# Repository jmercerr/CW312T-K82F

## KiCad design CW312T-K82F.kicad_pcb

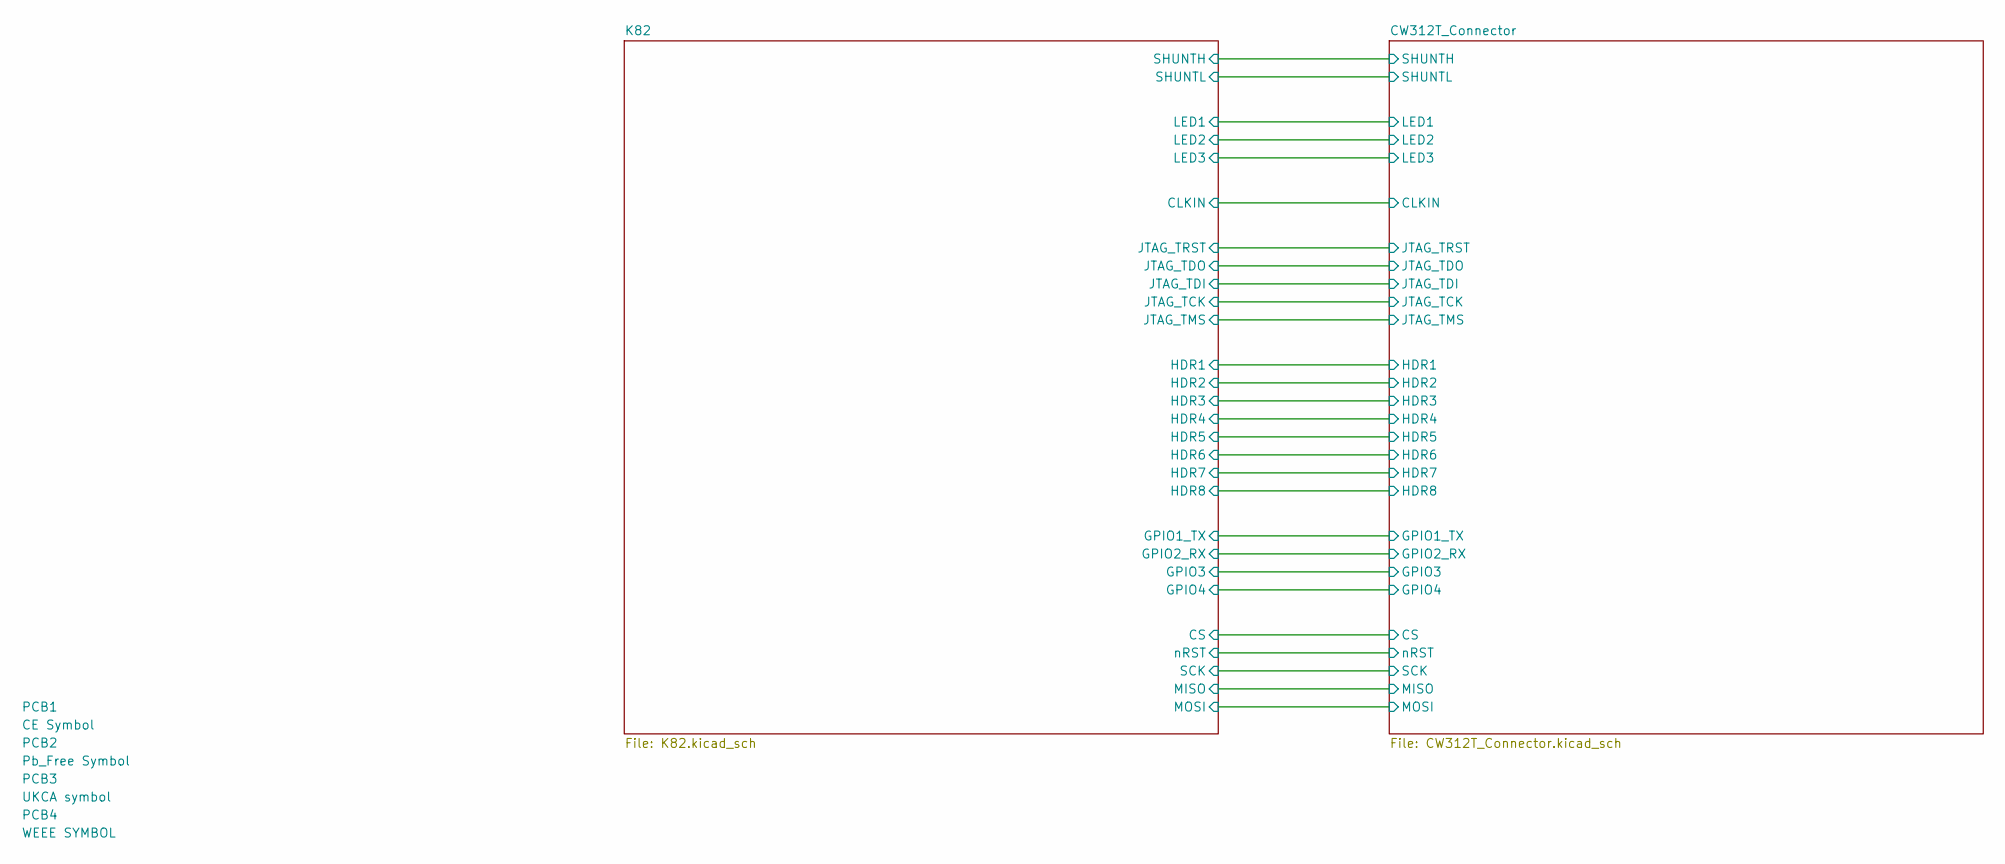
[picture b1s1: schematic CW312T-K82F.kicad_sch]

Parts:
PCB1: CE Symbol; CE-Logo_8.5x6mm_SilkScreen
PCB2: Pb_Free Symbol; Pb_Free_8.0x8.0mm_SilkScreen
PCB3: UKCA symbol; UKCA-Logo_8x8mm_SilkScreen
PCB4: WEEE SYMBOL; WEEE-Logo_5.6x8mm_SilkScreen

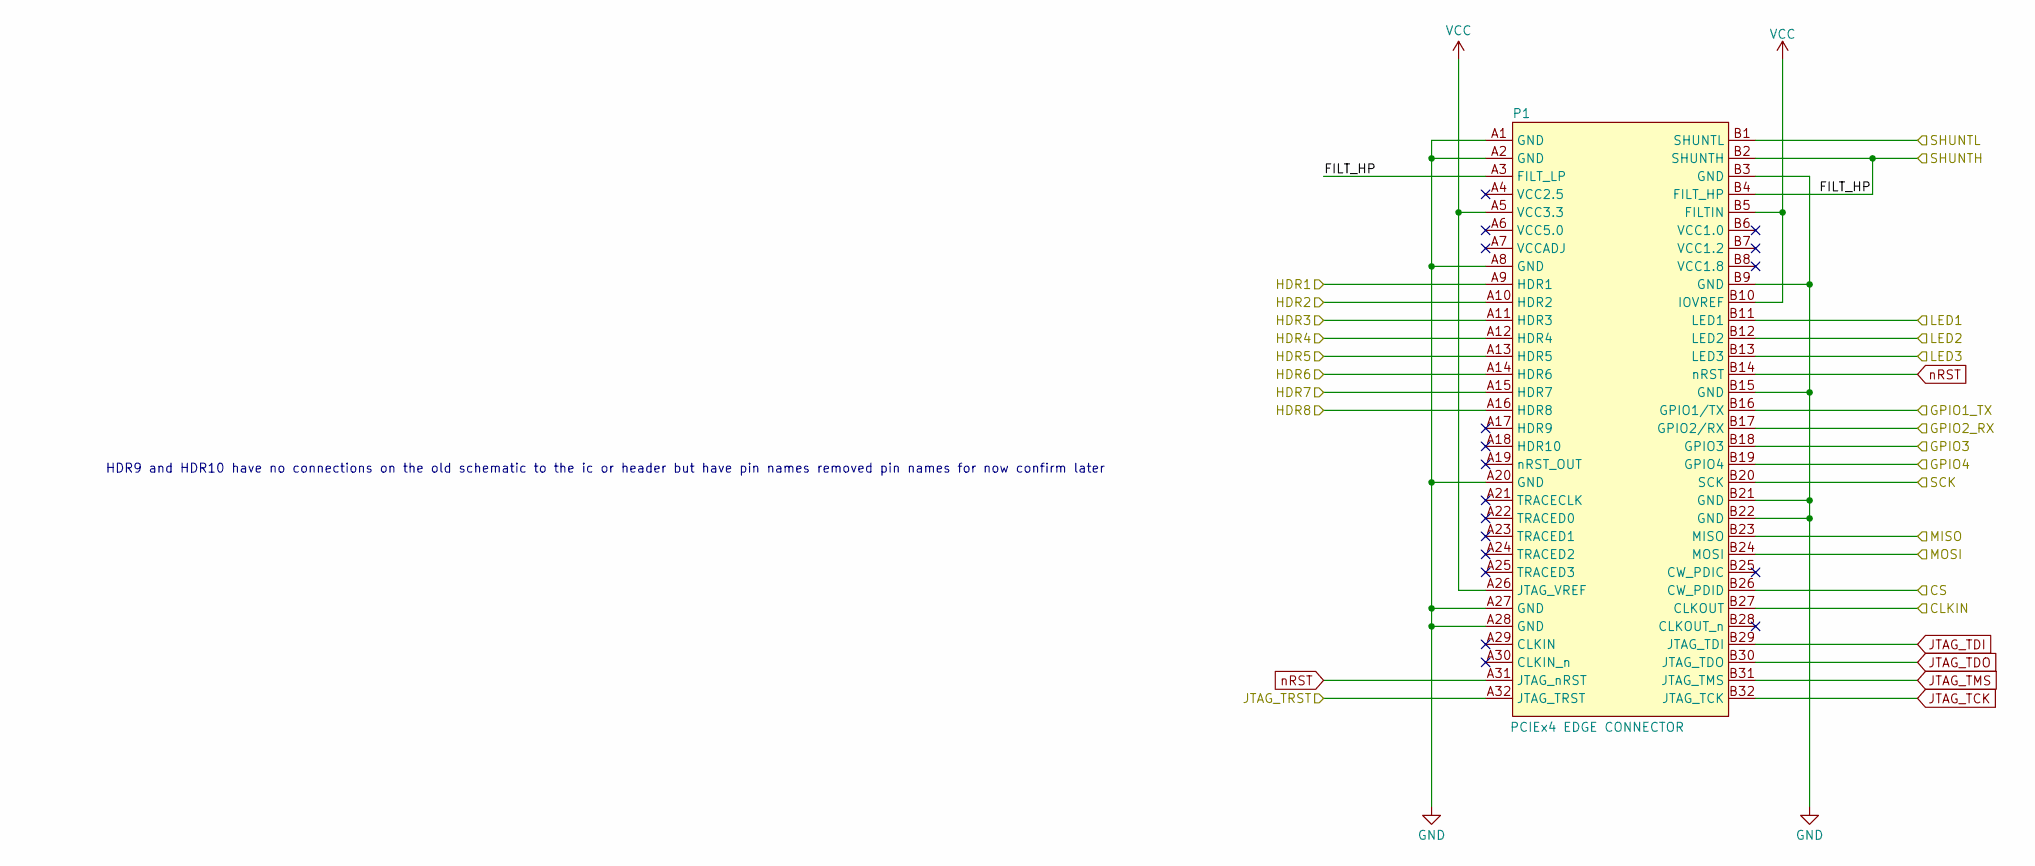
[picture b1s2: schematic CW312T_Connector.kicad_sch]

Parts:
P1: PCIEx4 EDGE CONNECTOR; CW312_Template

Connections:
/CW312T_Connector/CLKIN: P1.B27 (CLKOUT); also elsewhere on the board
/CW312T_Connector/CS: P1.B26 (CW_PDID); also elsewhere on the board
/CW312T_Connector/FILT_HP: P1.A3 (FILT_LP), P1.B2 (SHUNTH), P1.B4 (FILT_HP); also elsewhere on the board
/CW312T_Connector/GPIO1_TX: P1.B16 (GPIO1/TX); also elsewhere on the board
/CW312T_Connector/GPIO2_RX: P1.B17 (GPIO2/RX); also elsewhere on the board
/CW312T_Connector/GPIO3: P1.B18 (GPIO3); also elsewhere on the board
/CW312T_Connector/GPIO4: P1.B19 (GPIO4); also elsewhere on the board
/CW312T_Connector/HDR1: P1.A9 (HDR1); also elsewhere on the board
/CW312T_Connector/HDR2: P1.A10 (HDR2); also elsewhere on the board
/CW312T_Connector/HDR3: P1.A11 (HDR3); also elsewhere on the board
/CW312T_Connector/HDR4: P1.A12 (HDR4); also elsewhere on the board
/CW312T_Connector/HDR5: P1.A13 (HDR5); also elsewhere on the board
/CW312T_Connector/HDR6: P1.A14 (HDR6); also elsewhere on the board
/CW312T_Connector/HDR7: P1.A15 (HDR7); also elsewhere on the board
/CW312T_Connector/HDR8: P1.A16 (HDR8); also elsewhere on the board
/CW312T_Connector/JTAG_TRST: P1.A32 (JTAG_TRST); also elsewhere on the board
/CW312T_Connector/LED1: P1.B11 (LED1); also elsewhere on the board
/CW312T_Connector/LED2: P1.B12 (LED2); also elsewhere on the board
/CW312T_Connector/LED3: P1.B13 (LED3); also elsewhere on the board
/CW312T_Connector/MISO: P1.B23 (MISO); also elsewhere on the board
/CW312T_Connector/MOSI: P1.B24 (MOSI); also elsewhere on the board
/CW312T_Connector/SCK: P1.B20 (SCK); also elsewhere on the board
/CW312T_Connector/SHUNTL: P1.B1 (SHUNTL); also elsewhere on the board
GND: P1.A1 (GND), P1.A2 (GND), P1.A8 (GND), P1.A20 (GND), P1.A27 (GND), P1.A28 (GND), P1.B3 (GND), P1.B9 (GND), P1.B15 (GND), P1.B21 (GND), P1.B22 (GND); also elsewhere on the board
JTAG_TCK: P1.B32 (JTAG_TCK); also elsewhere on the board
JTAG_TDI: P1.B29 (JTAG_TDI); also elsewhere on the board
JTAG_TDO: P1.B30 (JTAG_TDO); also elsewhere on the board
JTAG_TMS: P1.B31 (JTAG_TMS); also elsewhere on the board
VCC: P1.A5 (VCC3.3), P1.A26 (JTAG_VREF), P1.B5 (FILTIN), P1.B10 (IOVREF); also elsewhere on the board
nRST: P1.A31 (JTAG_nRST), P1.B14 (nRST); also elsewhere on the board

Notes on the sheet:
HDR9 and HDR10 have no connections on the old schematic to the ic or header but have pin names removed pin names for now confirm later

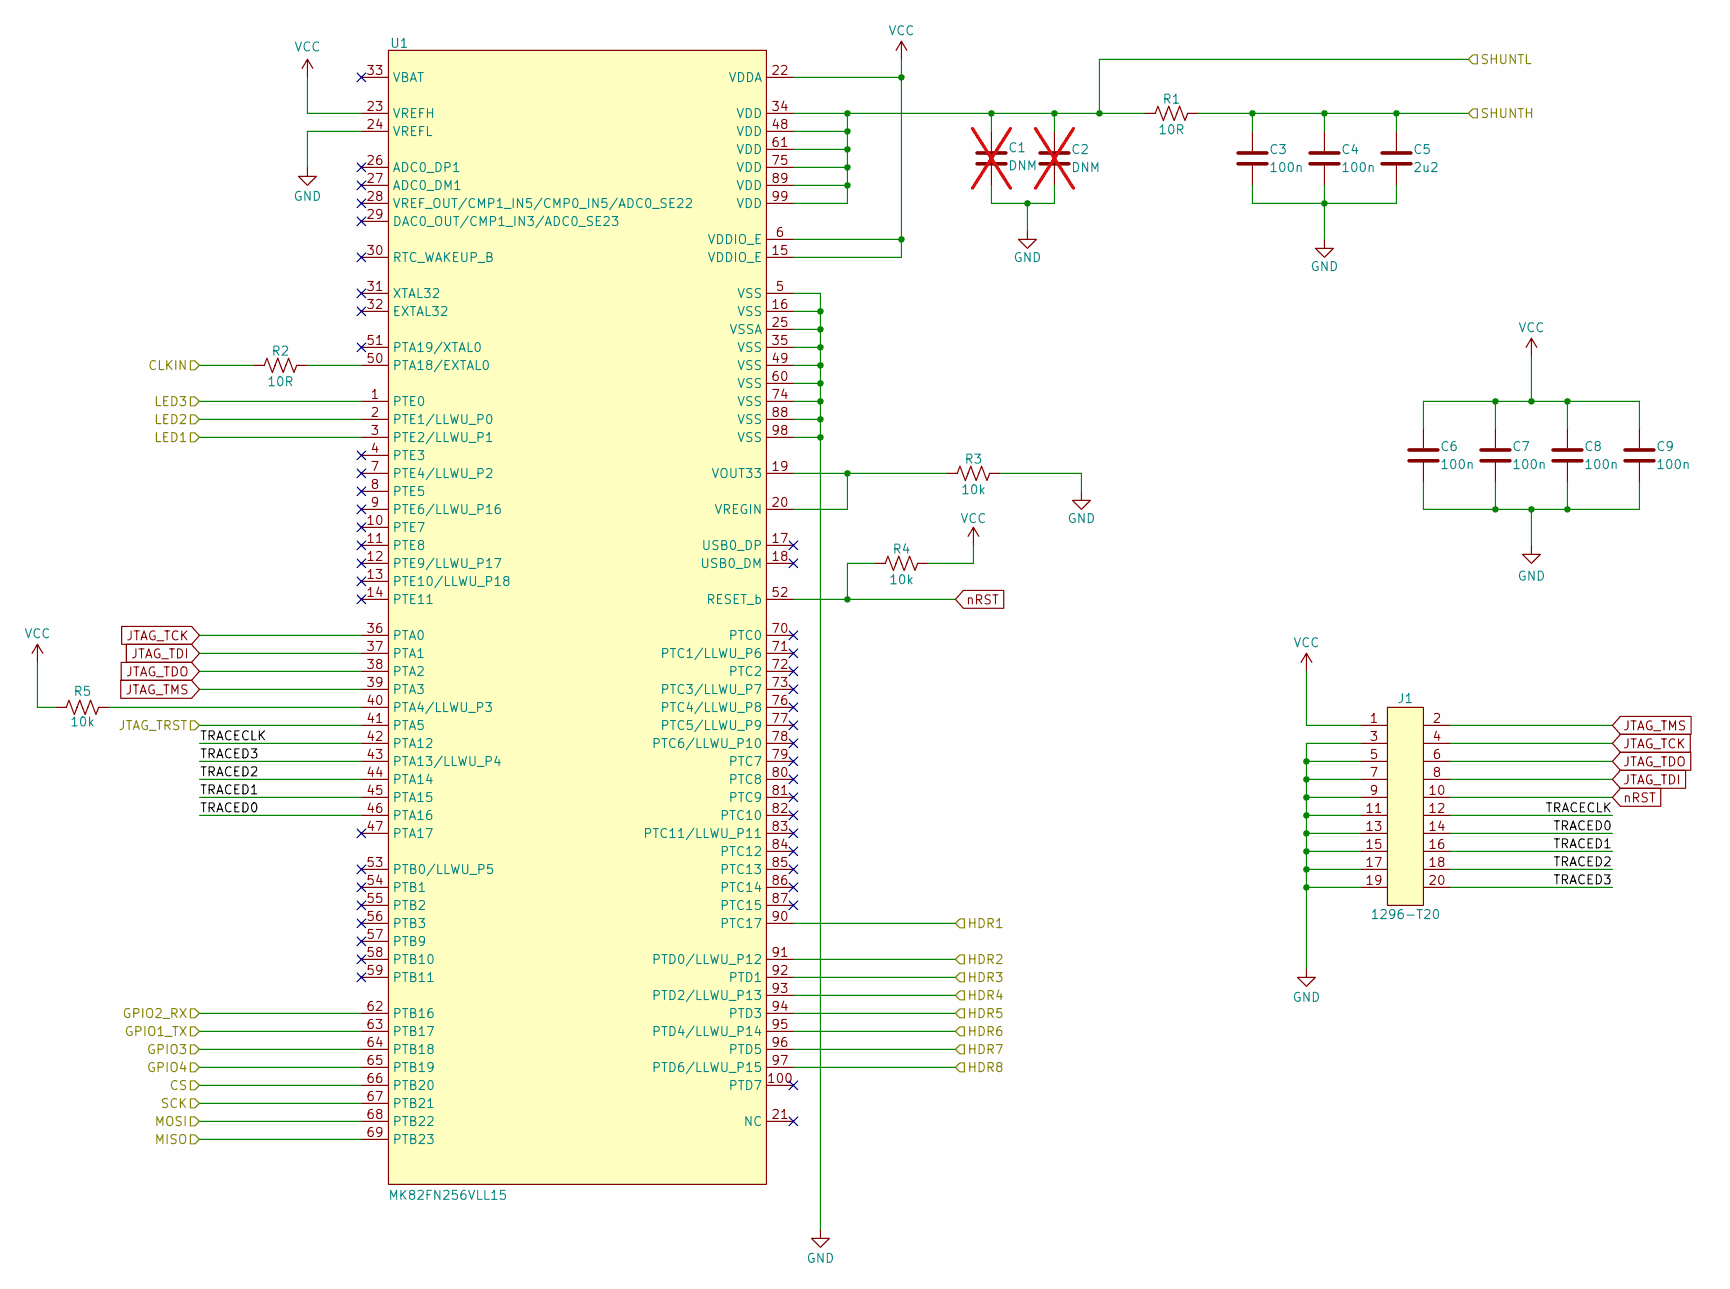
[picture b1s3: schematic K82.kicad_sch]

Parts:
C1, C2: DNM_CAP_0603; C_0603_1608Metric; Manufacturer Part Number C0603C225K4PAC7867; not fitted
C3, C4, C6, C7, C8, C9: CAP_100n_6.3V_0603; C_0603_1608Metric; Manufacturer Part Number CC0603KRX7R5BB104
C5: CAP_2u2_6.3V_0603; C_0603_1608Metric; Manufacturer Part Number CC0603KRX7R5BB225
J1: 20_pin; PinHeader_2x10_P1.00mm_Vertical_SMD; Manufacturer Part Number 20021121-00020T4LF
R1, R2: RES_10R_0603; R_0603_1608Metric; Manufacturer Part Number RC0603FR-0710RL
R3, R4, R5: RES_10k_0603; R_0603_1608Metric; Manufacturer Part Number RC0603FR-0710KL
U1: MK82FN256VLL15; LQFP-100_14x14mm_P0.5mm; Manufacturer Part Number MK82FN256VLL15

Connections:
/CW312T_Connector/CLKIN: R2.1; also elsewhere on the board
/CW312T_Connector/CS: U1.66 (PTB20); also elsewhere on the board
/CW312T_Connector/FILT_HP: C3.2, C4.2, C5.2, R1.2; also elsewhere on the board
/CW312T_Connector/GPIO1_TX: U1.63 (PTB17); also elsewhere on the board
/CW312T_Connector/GPIO2_RX: U1.62 (PTB16); also elsewhere on the board
/CW312T_Connector/GPIO3: U1.64 (PTB18); also elsewhere on the board
/CW312T_Connector/GPIO4: U1.65 (PTB19); also elsewhere on the board
/CW312T_Connector/HDR1: U1.90 (PTC17); also elsewhere on the board
/CW312T_Connector/HDR2: U1.91 (PTD0/LLWU_P12); also elsewhere on the board
/CW312T_Connector/HDR3: U1.92 (PTD1); also elsewhere on the board
/CW312T_Connector/HDR4: U1.93 (PTD2/LLWU_P13); also elsewhere on the board
/CW312T_Connector/HDR5: U1.94 (PTD3); also elsewhere on the board
/CW312T_Connector/HDR6: U1.95 (PTD4/LLWU_P14); also elsewhere on the board
/CW312T_Connector/HDR7: U1.96 (PTD5); also elsewhere on the board
/CW312T_Connector/HDR8: U1.97 (PTD6/LLWU_P15); also elsewhere on the board
/CW312T_Connector/JTAG_TRST: U1.41 (PTA5); also elsewhere on the board
/CW312T_Connector/LED1: U1.3 (PTE2/LLWU_P1); also elsewhere on the board
/CW312T_Connector/LED2: U1.2 (PTE1/LLWU_P0); also elsewhere on the board
/CW312T_Connector/LED3: U1.1 (PTE0); also elsewhere on the board
/CW312T_Connector/MISO: U1.69 (PTB23); also elsewhere on the board
/CW312T_Connector/MOSI: U1.68 (PTB22); also elsewhere on the board
/CW312T_Connector/SCK: U1.67 (PTB21); also elsewhere on the board
/CW312T_Connector/SHUNTL: C1.1, C2.1, R1.1, U1.34 (VDD), U1.48 (VDD), U1.61 (VDD), U1.75 (VDD), U1.89 (VDD), U1.99 (VDD); also elsewhere on the board
/K82/TRACECLK: J1.12, U1.42 (PTA12)
/K82/TRACED0: J1.14, U1.46 (PTA16)
/K82/TRACED1: J1.16, U1.45 (PTA15)
/K82/TRACED2: J1.18, U1.44 (PTA14)
/K82/TRACED3: J1.20, U1.43 (PTA13/LLWU_P4)
GND: C1.2, C2.2, C3.1, C4.1, C5.1, C6.1, C7.1, C8.1, C9.1, J1.3, J1.5, J1.7, J1.9, J1.11, J1.13, J1.15, J1.17, J1.19, R3.2, U1.5 (VSS), U1.16 (VSS), U1.24 (VREFL), U1.25 (VSSA), U1.35 (VSS), U1.49 (VSS), U1.60 (VSS), U1.74 (VSS), U1.88 (VSS), U1.98 (VSS); also elsewhere on the board
JTAG_TCK: J1.4, U1.36 (PTA0); also elsewhere on the board
JTAG_TDI: J1.8, U1.37 (PTA1); also elsewhere on the board
JTAG_TDO: J1.6, U1.38 (PTA2); also elsewhere on the board
JTAG_TMS: J1.2, U1.39 (PTA3); also elsewhere on the board
unnamed: R5.2, U1.40 (PTA4/LLWU_P3)
unnamed: R2.2, U1.50 (PTA18/EXTAL0)
unnamed: R3.1, U1.19 (VOUT33), U1.20 (VREGIN)
VCC: C6.2, C7.2, C8.2, C9.2, J1.1, R4.2, R5.1, U1.6 (VDDIO_E), U1.15 (VDDIO_E), U1.22 (VDDA), U1.23 (VREFH); also elsewhere on the board
nRST: J1.10, R4.1, U1.52 (RESET_b); also elsewhere on the board

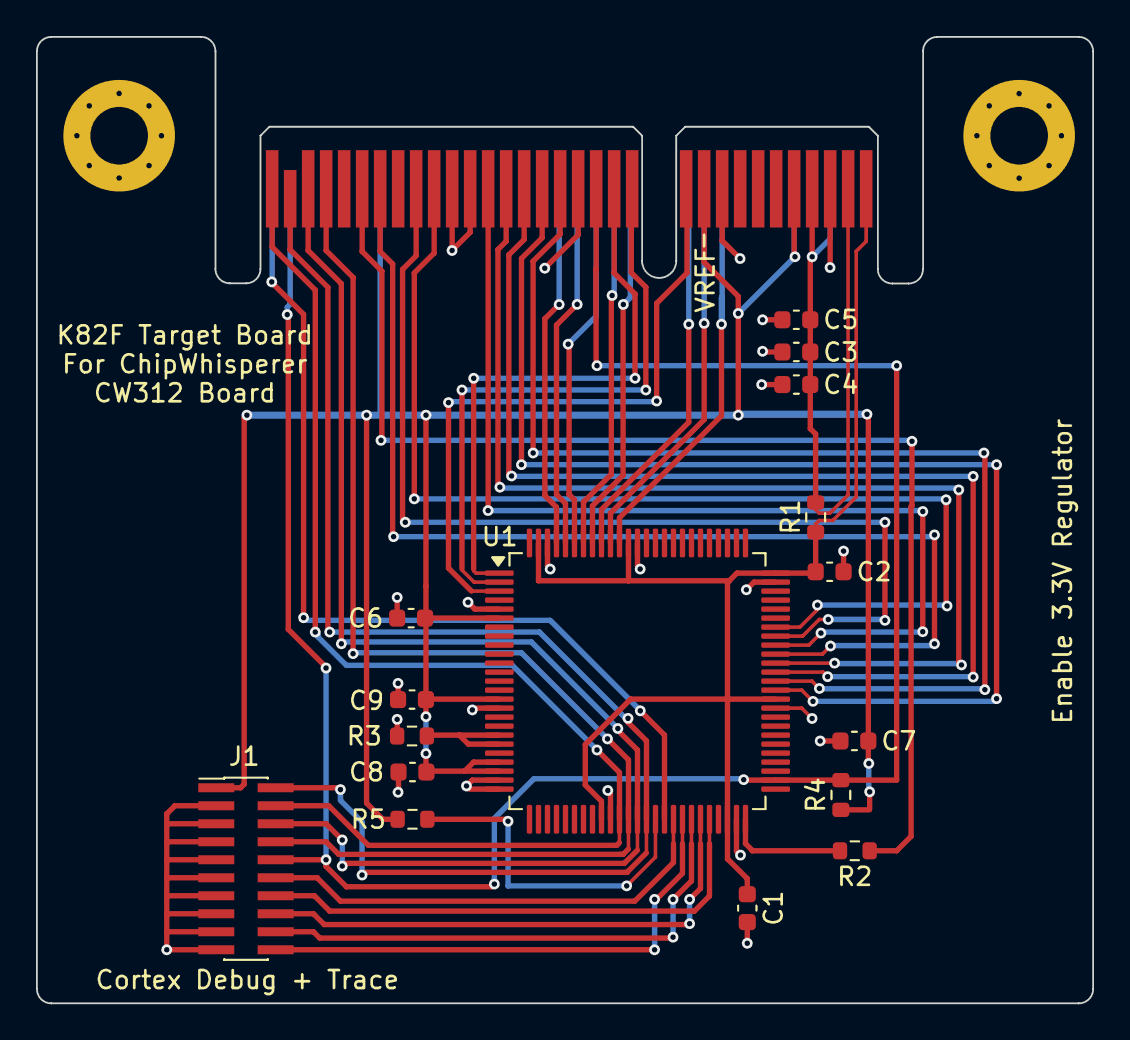
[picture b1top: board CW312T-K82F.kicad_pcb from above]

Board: 2 copper layers, 58.7 x 53.7 mm, 21 parts (0 on the bottom side), 38 nets.

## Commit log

2024-11-26 first draft - ready for review
2024-12-04 updated schematic and pcb - ready for review
2024-12-04 updated silkscreen and production files
2024-12-19 updated schematic and pcb after library re-organization
